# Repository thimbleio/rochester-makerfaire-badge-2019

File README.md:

# Rochester Maker Faire 2019 Solder Badge

This repository contains the KiCAD design files and Gerbers for the 2019 Rochester Maker Faire Badge

This badge was designed by David Brenner of [Thimble.io](http://www.thimble.io) with support provided by [Rochester MakerSpace](https://rocmakers.org/).and [NYSCATE](http://www.nyscate.org/).

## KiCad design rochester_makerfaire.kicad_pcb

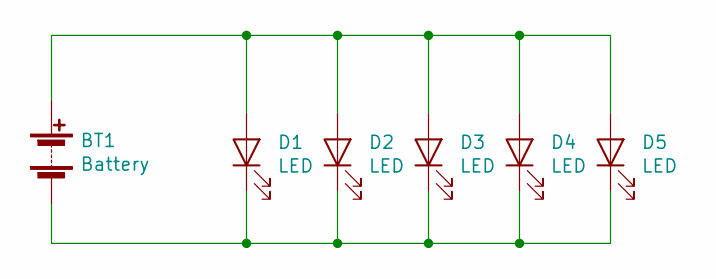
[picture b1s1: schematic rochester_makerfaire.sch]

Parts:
BT1: Battery; BatteryHolder_Keystone_3001_1x12mm
D1: LED; LED_D5.0mm
D2: LED; LED_1206_3216Metric
D3: LED; LED_0805_2012Metric
D4: LED; LED_0603_1608Metric
D5: LED; LED_0402_1005Metric

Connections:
unnamed: BT1.1 (+), D1.2 (A), D2.2 (A), D3.2 (A), D4.2 (A), D5.2 (A)
unnamed: BT1.2 (-), D1.1 (K), D2.1 (K), D3.1 (K), D4.1 (K), D5.1 (K)

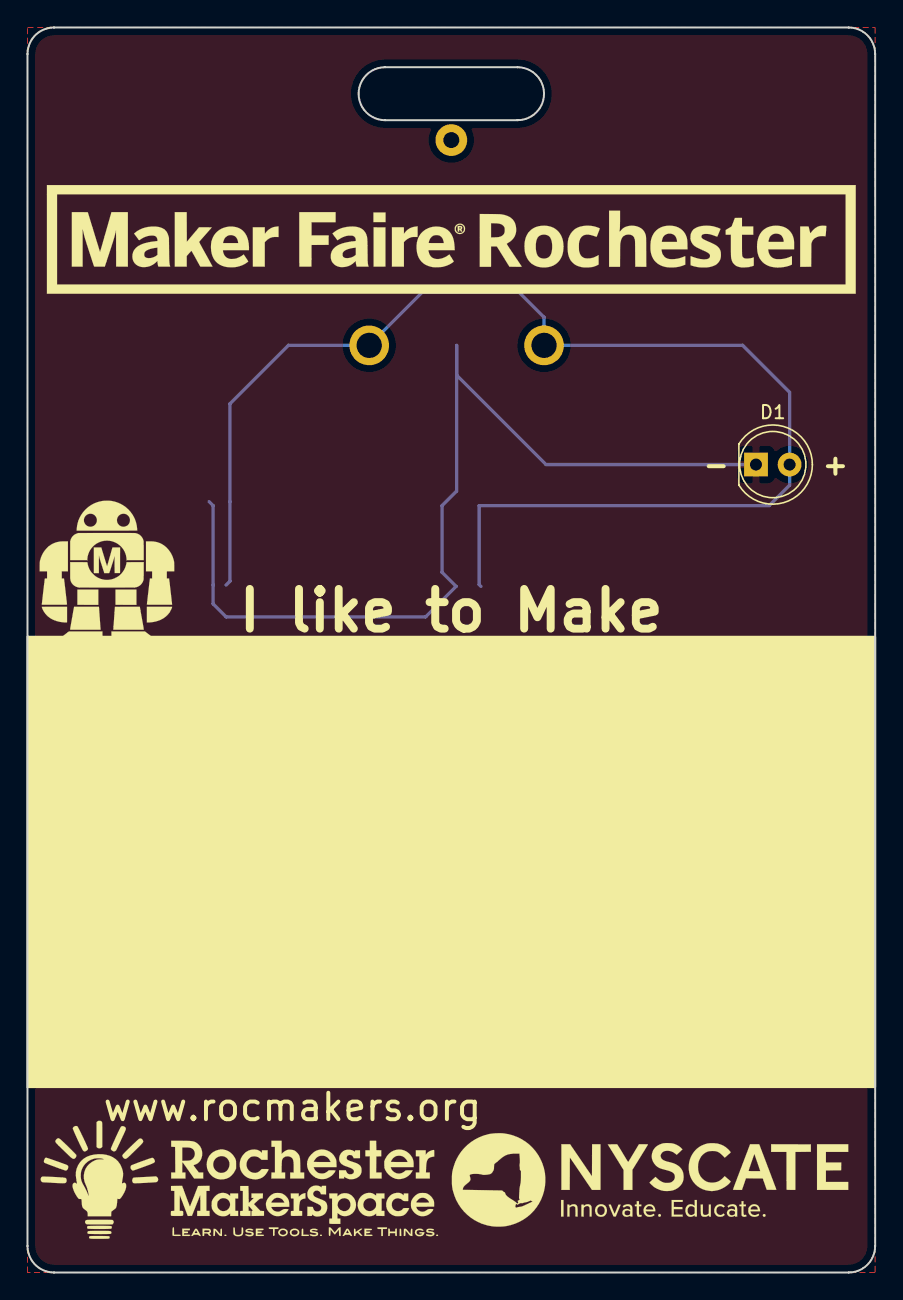
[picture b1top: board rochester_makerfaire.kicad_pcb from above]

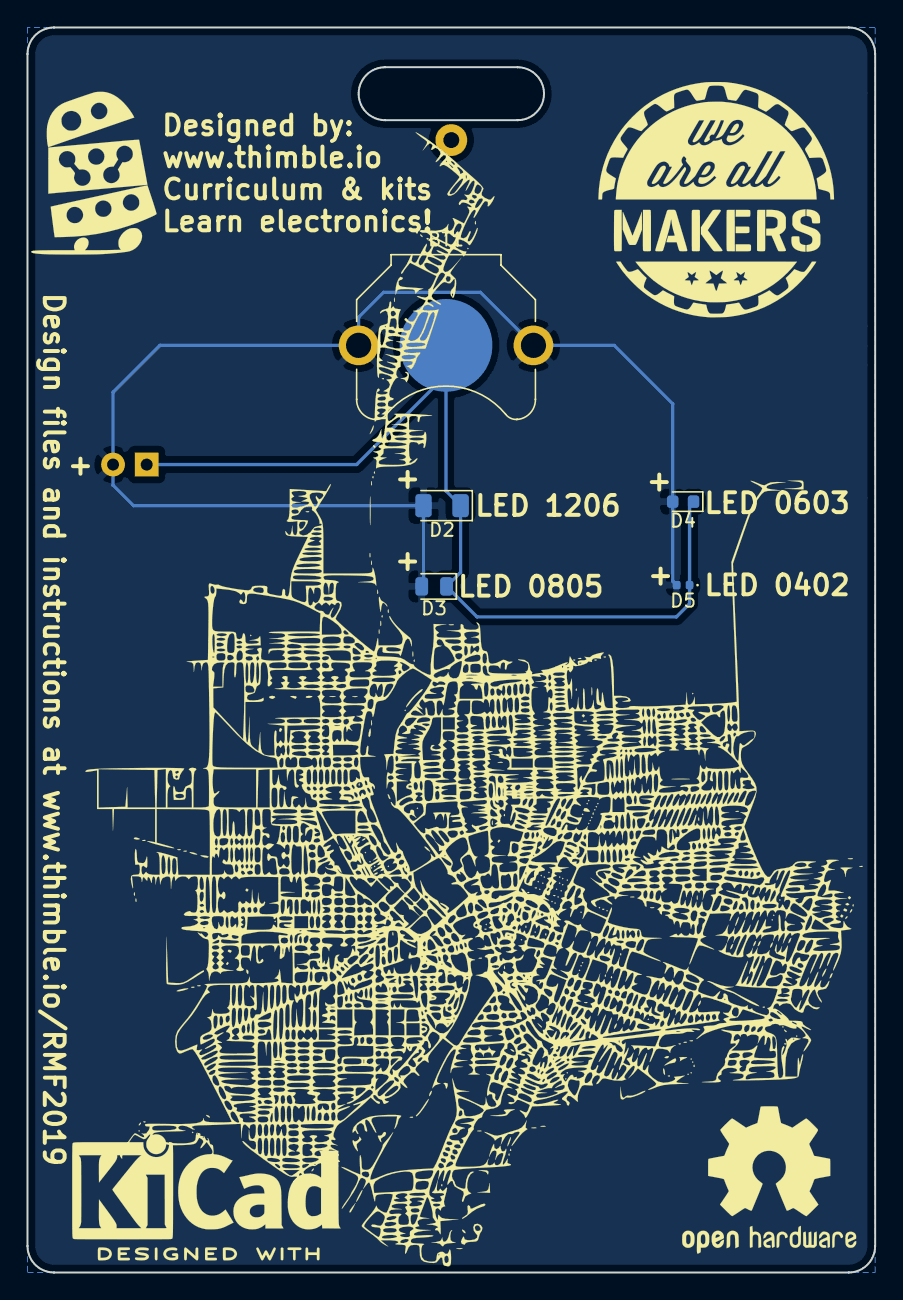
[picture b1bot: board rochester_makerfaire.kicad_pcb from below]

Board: 2 copper layers, 64.0 x 94.0 mm, 6 parts (5 on the bottom side), 2 nets.

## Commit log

2018-10-17 Initial commit - board outline and name plate
2018-10-17 First draft of the front of the badge.
2018-10-18 Add map of Rochester
2019-11-23 Add 2019 deign files
2019-11-23 Add README
